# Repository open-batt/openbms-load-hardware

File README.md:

# OpenBMS Load

**OpenBMS Load** is a hardware design of a resistive load used for battery discharging. Its main purpose is testing the battery management system (BMS) during charge and discharge cycles.

## How OpenBMS Load fits into system?

Battery system consists of:

- Li-ion/Li-po battery - your custom 2 to 7-cell battery
- [OpenBMS](https://github.com/open-batt/openbms-hardware)
- Host - I2C/CAN interfaces, wake-up signal, can be a microcontroller, computer, etc.
- Load - your piece of equipment that draws energy from the battery. In this case, we provide OpenBMS-load-hardware, a 600W resistive load for easier BMS development and testing
- Charger - your custom charger, usually a CC/CV charger adjusted to your battery voltage and current

## Features

- 🔥 Twenty 25-ohm 50W resistors to dissipate up to 600W
- 🔛  Jumpers / 5A fuse - each resistor has jumper/fuse to enable it or disable it - this way total load resistance can be adjusted from 1 to 20 ohms
- 🔌 Male XT60 connector for BMS (battery) connection
- 🔌 Female XT60 connector for charger connection
- 🔄 Tri state switch:
  - 1 - Battery discharging - energy flows from battery to load (resistors)
  - 2 - Battery charging - energy flows from charger to battery (resistors are bypassed and not used)
  - 3 - Idling - battery is neither charging nor discharging
- 💨 Six fans to blow heat from resistors - speed adjustable by potentiometer
- 🟢 Green LED to indicate that charger is present
- 🔴 Red LED to indicate that battery is discharging
  
## Overview

The OpenBMS 600W Resistive Load is a purpose-built battery testing board designed to work alongside the OpenBMS system. 

It carries twenty 25Ω 50W wirewound resistors arranged across the board, capable of dissipating up to 600W of power. Each resistor is individually switchable via a jumper and protected by a 5A fuse, allowing the total load resistance to be adjusted between 1 and 20 ohms. 

Six cooling fans keep the resistors from overheating, with speed controlled by an onboard potentiometer. 

Two XT60 connectors handle battery and charger connections, and a three-position switch selects between discharging (energy flows from battery into the resistors), charging (charger feeds the battery directly, bypassing the resistors), and idle mode. 

A green LED signals charger presence and a red LED indicates active discharging.

## ❤️ Funding

This project is funded through [NGI0 Commons Fund](https://nlnet.nl/commonsfund), a fund established by [NLnet](https://nlnet.nl) with financial support from the European Commission's [Next Generation Internet](https://ngi.eu) program. 

We are very grateful to the NLnet team for helping us on our path, and we encourage you too to apply and get funds to build your project! 🚀
Learn more at the [NLnet project page](https://nlnet.nl/project/OpenBMS).

## License

OpenBMS-Load is licensed under CERN OHL-S v2 license.

Check [openbatt.dev](https://openbatt.dev) for more!

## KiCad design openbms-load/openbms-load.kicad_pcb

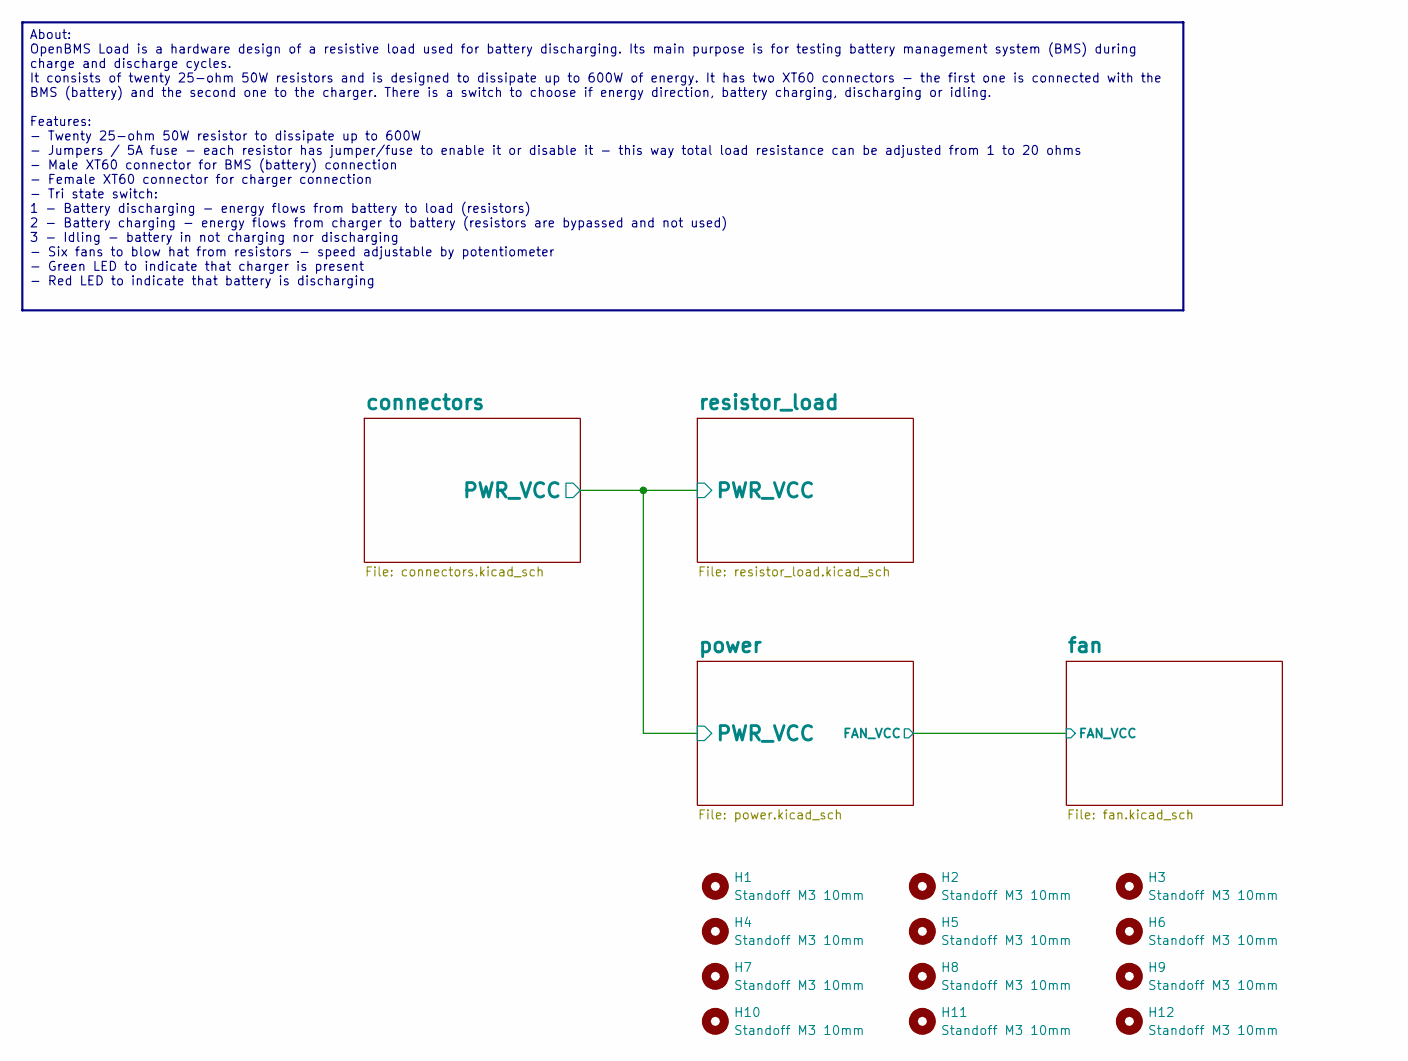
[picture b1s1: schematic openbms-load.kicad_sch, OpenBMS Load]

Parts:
H1, H2, H3, H4, H5, H6, H7, H8, H9, H10, H11, H12: Standoff M3 10mm; 24433; Manufacturer_Part_Number 24433

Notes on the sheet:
About: OpenBMS Load is a hardware design of a resistive load used for battery discharging. Its main purpose is for testing battery management system (BMS) during charge and discharge cycles. It consists of twenty 25-ohm 50W resistors and is designed to dissipate up to 600W of energy. It has two XT6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

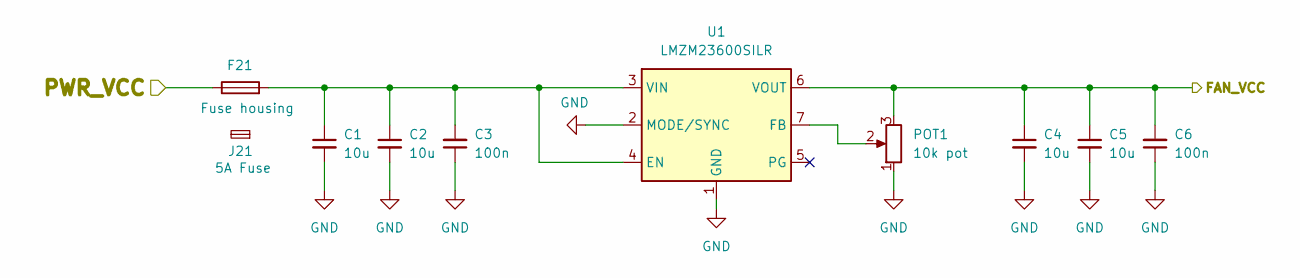
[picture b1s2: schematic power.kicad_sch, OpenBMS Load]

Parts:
C1, C2, C4, C5: 10u; C_1206_3216Metric; Manufacturer_Part_Number CL31A106MBHNNNE
C3, C6: 100n; C_0402_1005Metric; Manufacturer_Part_Number GRM155R71A104KA01D
F21: Fuse housing; 3568; Manufacturer_Part_Number 3568
J21: 5A Fuse; 0297005.WXNV; Manufacturer_Part_Number 0297005.WXNV
POT1: 10k pot; TC33X2503E; Manufacturer_Part_Number TC33X-2-103E
U1: LMZM23600SILR; Manufacturer_Part_Number LMZM23600SILR

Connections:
+PWR_VCC: F21.1; also elsewhere on the board
+VFAN: C4.1, C5.1, C6.2, POT1.3, U1.6 (VOUT); also elsewhere on the board
GND: C1.2, C2.2, C3.1, C4.2, C5.2, C6.1, POT1.1, U1.1 (GND), U1.2 (MODE/SYNC), U1.11 (GND); also elsewhere on the board
unnamed: C1.1, C2.1, C3.2, F21.2, U1.3 (VIN), U1.4 (EN)
unnamed: POT1.2, U1.7 (FB)

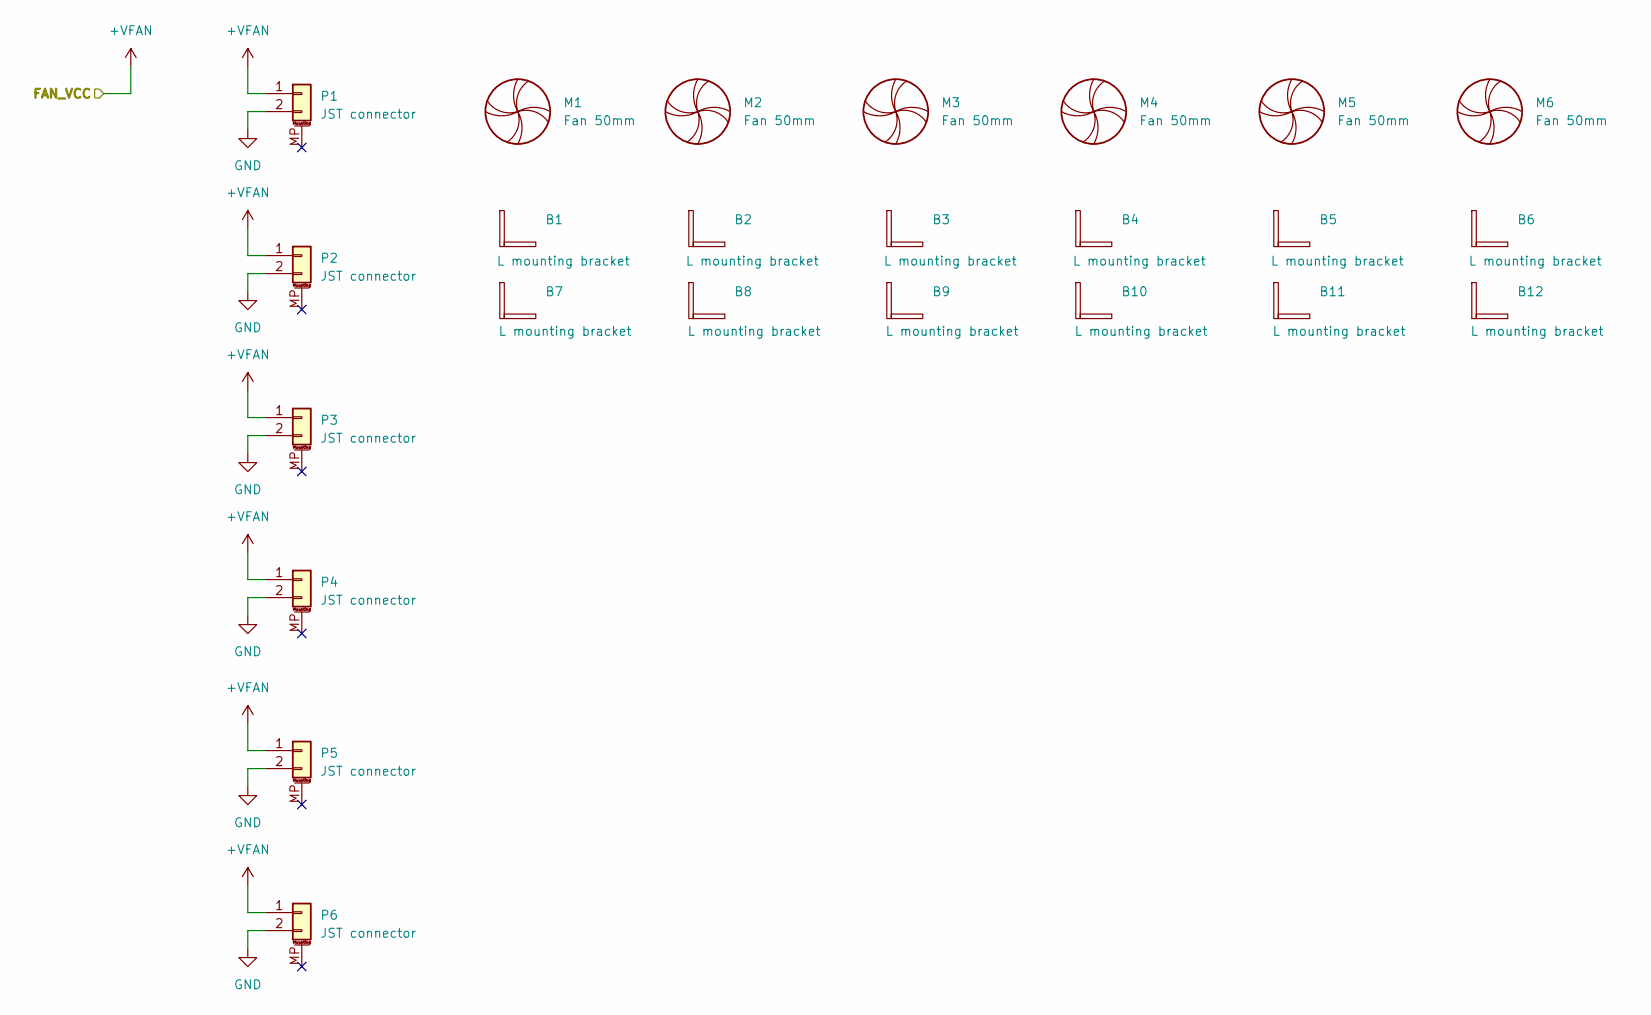
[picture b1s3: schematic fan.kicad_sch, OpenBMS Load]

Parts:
B1, B2, B3, B4, B5, B6, B7, B8, B9, B10, B11, B12: L mounting bracket; 633; Manufacturer_Part_Number 633
M1, M2, M3, M4, M5, M6: Fan 50mm; fan_MF50101V1-1000U-A99; Manufacturer_Part_Number MF50101V1-1000U-A99
P1, P2, P3, P4, P5, P6: JST connector; JST_PH_S2B-PH-SM4-TB_1x02-1MP_P2.00mm_Horizontal; Manufacturer_Part_Number S2B-PH-SM4-TB

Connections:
+VFAN: P1.1, P2.1, P3.1, P4.1, P5.1, P6.1; also elsewhere on the board
GND: P1.2, P2.2, P3.2, P4.2, P5.2, P6.2; also elsewhere on the board

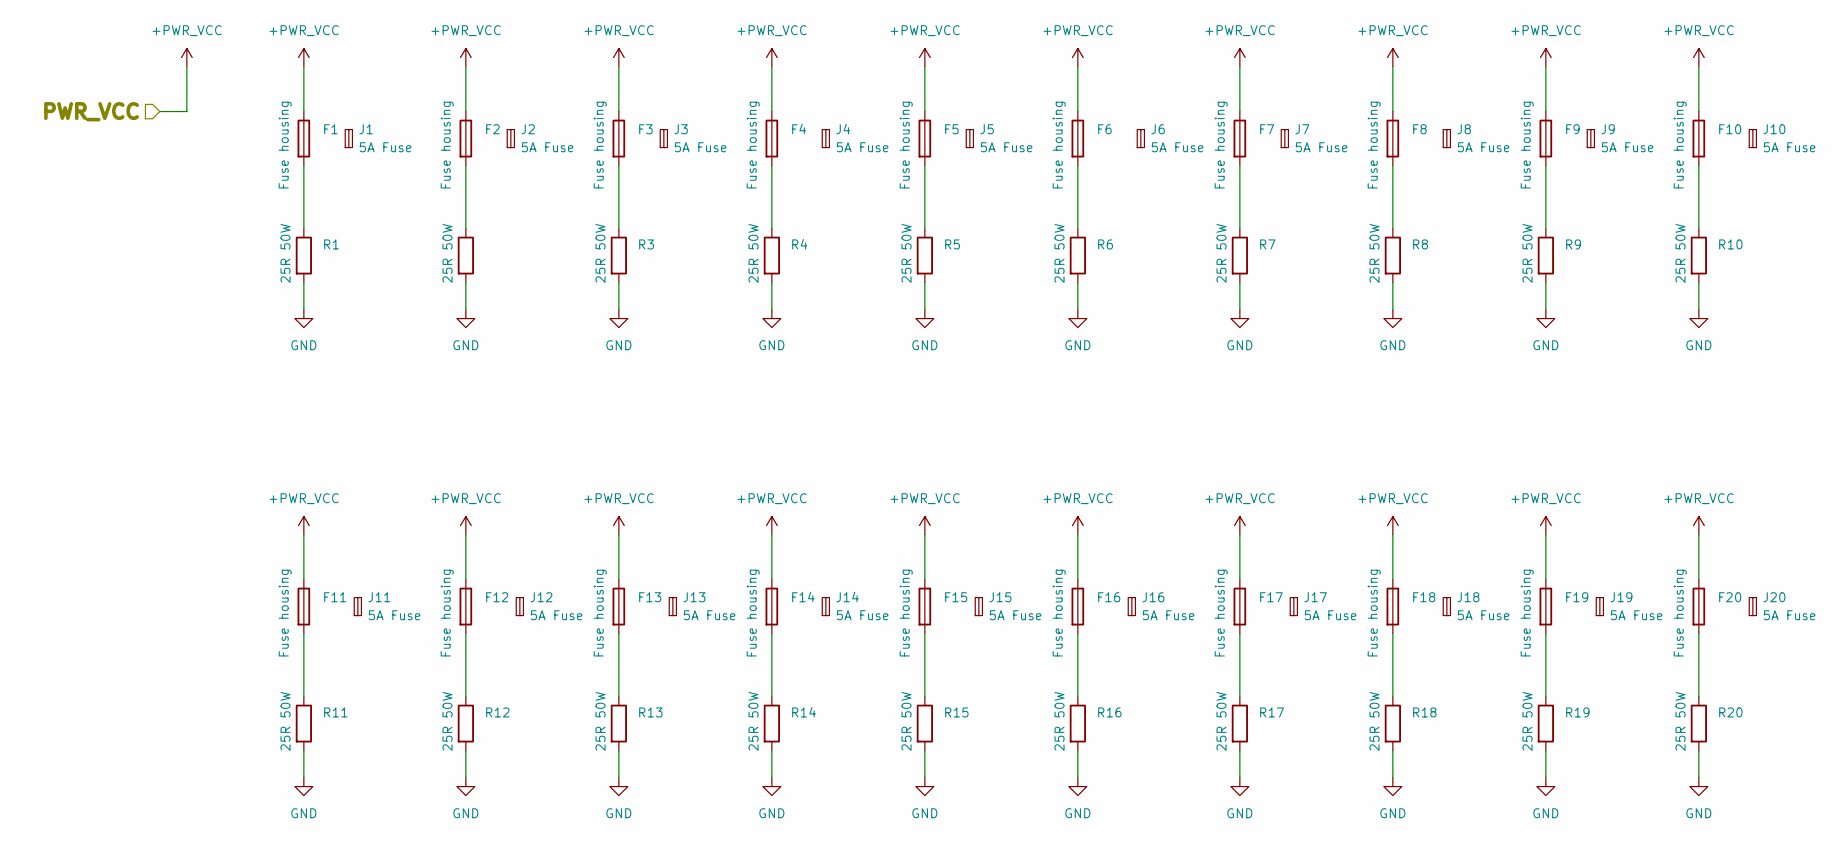
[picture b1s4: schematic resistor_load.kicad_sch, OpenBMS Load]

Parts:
F1, F2, F3, F4, F5, F6, F7, F8, F9, F10, F11, F12, F13, F14, F15, F16, F17, F18, F19, F20: Fuse housing; 3568; Manufacturer_Part_Number 3568
J1, J2, J3, J4, J5, J6, J7, J8, J9, J10, J11, J12, J13, J14, J15, J16, J17, J18, J19, J20: 5A Fuse; 0297005.WXNV; Manufacturer_Part_Number 0297005.WXNV
R1, R2, R3, R4, R5, R6, R7, R8, R9, R10, R11, R12, R13, R14, R15, R16, R17, R18, R19, R20: 25R 50W; L50J25RE; Manufacturer_Part_Number L50J25RE

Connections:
+PWR_VCC: F1.1, F2.1, F3.1, F4.1, F5.1, F6.1, F7.1, F8.1, F9.1, F10.1, F11.1, F12.1, F13.1, F14.1, F15.1, F16.1, F17.1, F18.1, F19.1, F20.1; also elsewhere on the board
GND: R1.2, R2.2, R3.2, R4.2, R5.2, R6.2, R7.2, R8.2, R9.2, R10.2, R11.2, R12.2, R13.2, R14.2, R15.2, R16.2, R17.2, R18.2, R19.2, R20.2; also elsewhere on the board
unnamed: F1.2, R1.1
unnamed: F2.2, R2.1
unnamed: F3.2, R3.1
unnamed: F4.2, R4.1
unnamed: F5.2, R5.1
unnamed: F6.2, R6.1
unnamed: F7.2, R7.1
unnamed: F8.2, R8.1
unnamed: F9.2, R9.1
unnamed: F10.2, R10.1
unnamed: F11.2, R11.1
unnamed: F12.2, R12.1
unnamed: F13.2, R13.1
unnamed: F14.2, R14.1
unnamed: F15.2, R15.1
unnamed: F16.2, R16.1
unnamed: F17.2, R17.1
unnamed: F18.2, R18.1
unnamed: F19.2, R19.1
unnamed: F20.2, R20.1

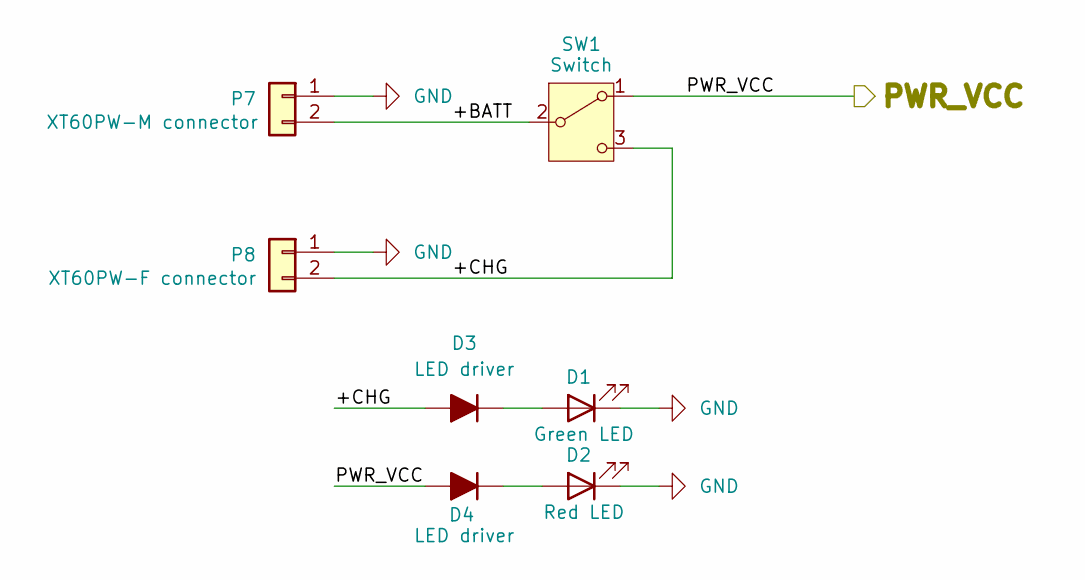
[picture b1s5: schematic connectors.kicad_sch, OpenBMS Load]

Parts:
D1: Green LED; LED_0603_1608Metric; Manufacturer_Part_Number LTST-S270KGKT
D2: Red LED; LED_0603_1608Metric; Manufacturer_Part_Number LTST-C190KRKT
D3, D4: LED driver; AL5809-15P1-7; Manufacturer_Part_Number AL5809-15P1-7
P7: XT60PW-M connector; AMASS_XT60PW-M_1x02_P7.20mm_Horizontal; Manufacturer_Part_Number XT60PW-M
P8: XT60PW-F connector; AMASS_XT60PW-F_1x02_P7.20mm_Horizontal; Manufacturer_Part_Number XT60PW-F
SW1: Switch; VRS-3-Q3PSI-19KNN-0-M2; Manufacturer_Part_Number VRS-3-Q3PSI-19KNN-0-M2

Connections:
+PWR_VCC: D4.2 (A), SW1.1 (A); also elsewhere on the board
/connectors/+BATT: P7.2, SW1.2 (B)
/connectors/+CHG: D3.2 (A), P8.2, SW1.3 (C)
GND: D1.1 (K), D2.1 (K), P7.1, P8.1; also elsewhere on the board
unnamed: D1.2 (A), D3.1 (K)
unnamed: D2.2 (A), D4.1 (K)

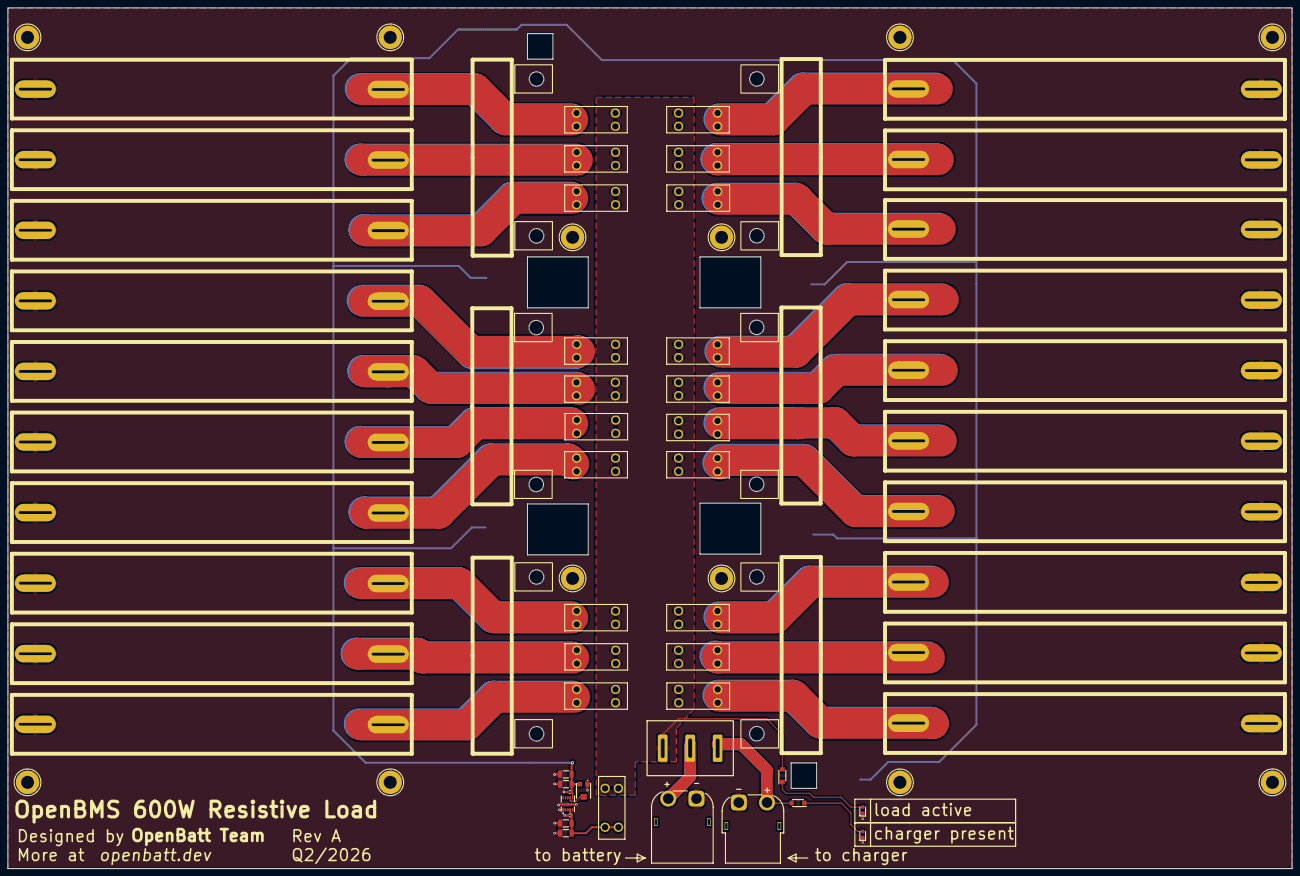
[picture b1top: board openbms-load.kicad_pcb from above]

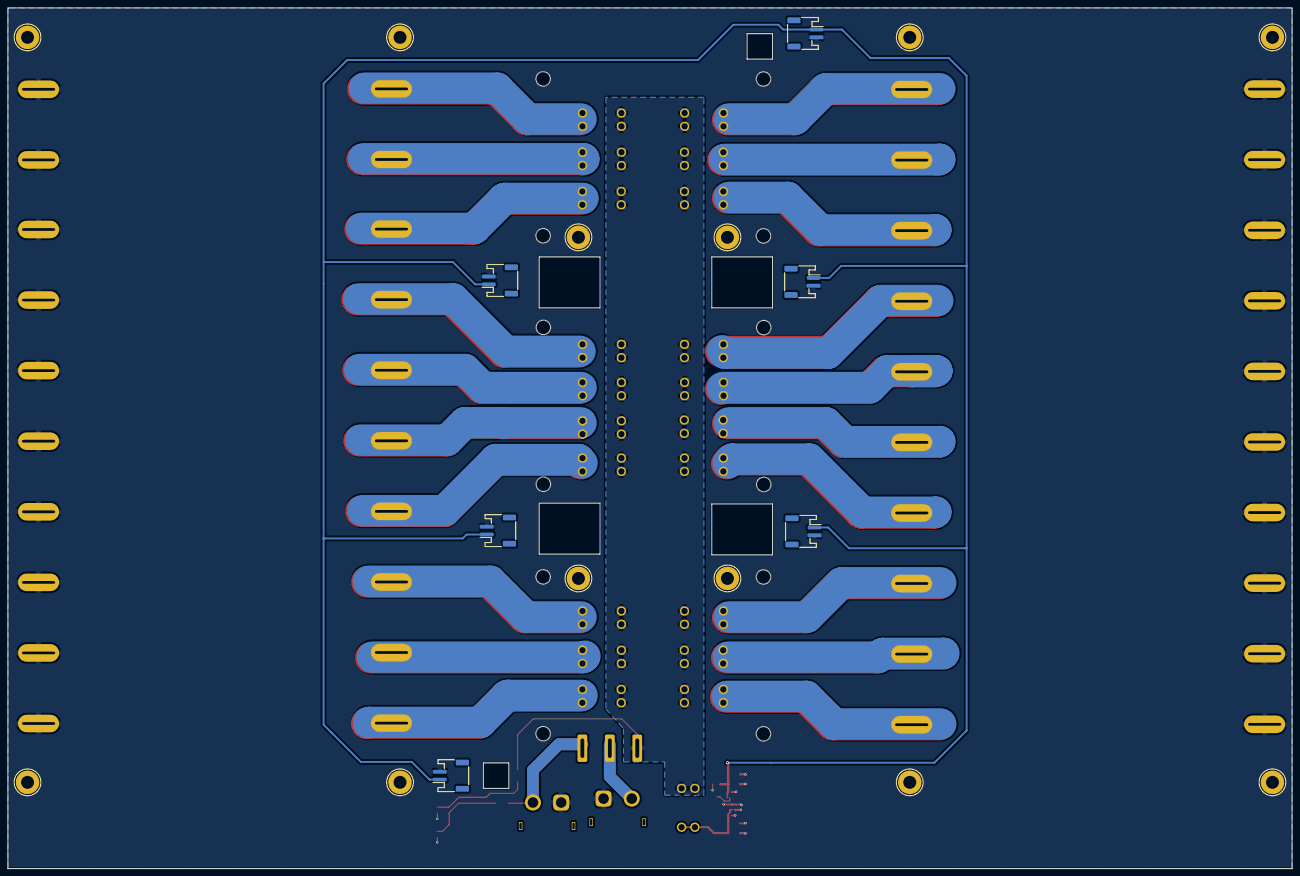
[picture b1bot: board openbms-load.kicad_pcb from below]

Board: 2 copper layers, 327.5 x 219.5 mm, 113 parts (18 on the bottom side), 29 nets.

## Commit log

2026-04-16 Initial commit, schematic and PCB layout Rev A release
2026-04-17 Images added, schematic PDF created
2026-04-17 PCB label updated, project images added
2026-04-17 Schematic description updated
2026-04-21 Production files release

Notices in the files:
README.md:
License: CERN-OHL-S-v2
